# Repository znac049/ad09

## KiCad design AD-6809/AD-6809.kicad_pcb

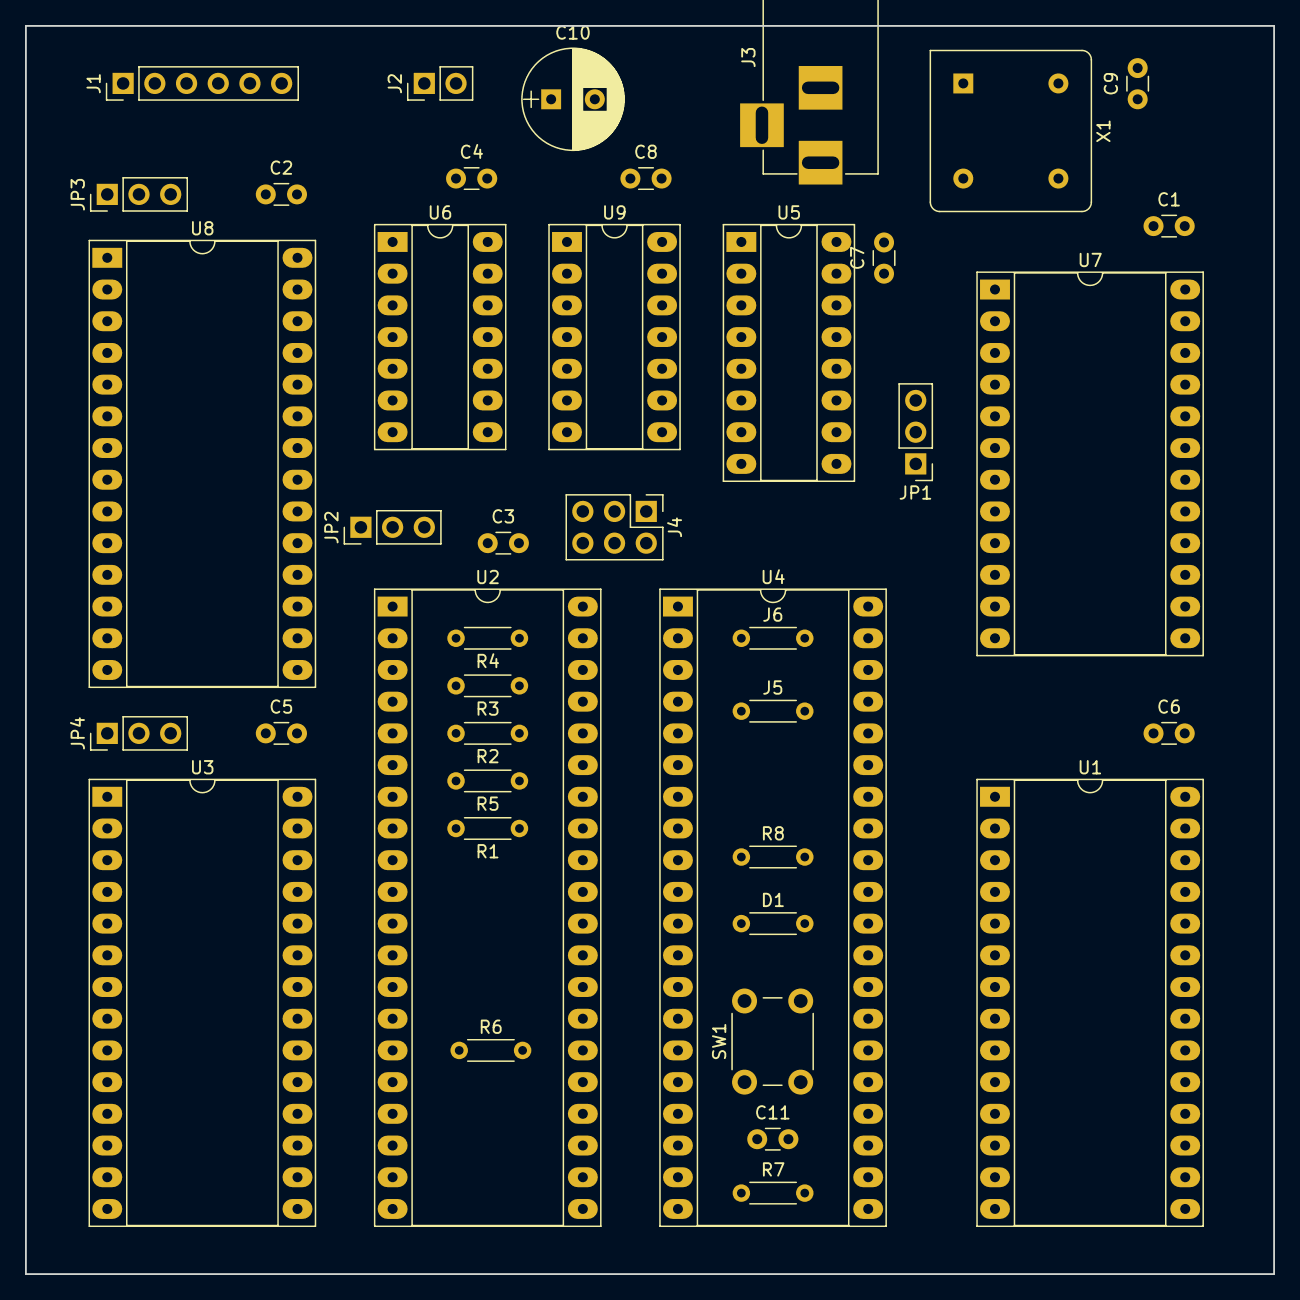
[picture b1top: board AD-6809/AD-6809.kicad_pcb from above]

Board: 2 copper layers, 100.0 x 100.0 mm, 41 parts (0 on the bottom side), 61 nets, no tracks yet.

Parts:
C1, C2, C3, C4, C5, C6, C7, C8, C9: 0.1uF; C_Disc_D3.0mm_W1.6mm_P2.50mm
C10: 470uF; CP_Radial_D8.0mm_P3.50mm
C11: 470nF; C_Disc_D3.0mm_W1.6mm_P2.50mm
D1: IN4148; R_Axial_DIN0204_L3.6mm_D1.6mm_P5.08mm_Horizontal
J1: SERIAL; Socket_Strip_Straight_1x06_Pitch2.54mm
J2: GAMECLK; Socket_Strip_Straight_1x02_Pitch2.54mm
J3: BARREL_JACK
J4: BAUD; Pin_Header_Straight_2x03_Pitch2.54mm
J5: NMI; R_Axial_DIN0204_L3.6mm_D1.6mm_P5.08mm_Horizontal
J6: RESET; R_Axial_DIN0204_L3.6mm_D1.6mm_P5.08mm_Horizontal
JP1: Disable; Socket_Strip_Straight_1x03_Pitch2.54mm
JP2: CLKSRC; Socket_Strip_Straight_1x03_Pitch2.54mm
JP3, JP4: ROM RAM; Socket_Strip_Straight_1x03_Pitch2.54mm
R1, R2, R3, R4, R5, R6, R8: 10K; R_Axial_DIN0204_L3.6mm_D1.6mm_P5.08mm_Horizontal
R7: 100R; R_Axial_DIN0204_L3.6mm_D1.6mm_P5.08mm_Horizontal
SW1: RESET; SW_PUSH_6mm
U1: 28C64; DIP-28_W15.24mm_Socket_LongPads
U2: 6809; DIP-40_W15.24mm_Socket_LongPads
U3, U8: 28C64/IMS1630; DIP-28_W15.24mm_Socket_LongPads
U4: 6502_Header; DIP-40_W15.24mm_Socket_LongPads
U5: 74LS139; DIP-16_W7.62mm_Socket_LongPads
U6: 74LS00; DIP-14_W7.62mm_Socket_LongPads
U7: MC6850; DIP-24_W15.24mm_Socket_LongPads
U9: 74LS93; DIP-14_W7.62mm_Socket_LongPads
X1: 12.288MHz; Oscillator_DIP-8

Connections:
+5V: C1.1, C2.1, C3.1, C4.1, C5.1, C6.1, C7.1, C8.1, C9.1, C10.1, D1.1, J3.1, J5.2, JP3.3, JP4.3, R1.1, R2.1, R3.1, R4.1, R5.1, R8.1, U1.28, U2.7, U3.28, U4.8, U5.16, U6.14, U7.10, U7.12, U8.28, U9.5, X1.1, X1.8
/A0: U1.10, U2.8, U3.10, U4.9, U7.11, U8.10
/A1: U1.9, U2.9, U3.9, U4.10, U8.9
/A2: U1.8, U2.10, U3.8, U4.11, U8.8
/A3: U1.7, U2.11, U3.7, U4.12, U8.7
/A4: U1.6, U2.12, U3.6, U4.13, U8.6
/A5: U1.5, U2.13, U3.5, U4.14, U8.5
/A6: U1.4, U2.14, U3.4, U4.15, U8.4
/A7: U1.3, U2.15, U3.3, U4.16, U8.3
/A8: U1.25, U2.16, U3.25, U4.17, U8.25
/A9: U1.24, U2.17, U3.24, U4.18, U8.24
/A10: U1.21, U2.18, U3.21, U4.19, U8.21
/A11: U1.23, U2.19, U3.23, U4.20, U5.14, U8.23
/A12: U1.2, U2.20, U3.2, U4.22, U5.13, U8.2
/A13: U2.21, U4.23, U5.2
/A14: U2.22, U4.24, U5.3
/A15: JP1.3, U2.23, U4.25, U6.4, U6.5
/CPUCLK: JP2.3, U9.1, U9.12
/D0: U1.11, U2.31, U3.11, U4.33, U7.22, U8.11
/D1: U1.12, U2.30, U3.12, U4.32, U7.21, U8.12
/D2: U1.13, U2.29, U3.13, U4.31, U7.20, U8.13
/D3: U1.15, U2.28, U3.15, U4.30, U7.19, U8.15
/D4: U1.16, U2.27, U3.16, U4.29, U7.18, U8.16
/D5: U1.17, U2.26, U3.17, U4.28, U7.17, U8.17
/D6: U1.18, U2.25, U3.18, U4.27, U7.16, U8.18
/D7: U1.19, U2.24, U3.19, U4.26, U7.15, U8.19
/PHI2: U2.34, U4.39, U6.10, U6.13, U7.14
/R/~W: U2.32, U4.34, U6.1, U6.2, U6.9, U7.13
/RXD: J1.3, U7.2
/SERCLK: J4.2, J4.4, J4.6, U7.3, U7.4
/TXD: J1.2, U7.6
/~A15: U5.1, U6.6
/~FIRQ: R3.2, U2.4
/~IRQ: R4.2, U2.3, U7.7
/~MEM1: U3.20, U5.5
/~MEM2: U5.6, U8.20
/~MEM3: U1.20, U5.7
/~NMI: R6.2, U2.2, U4.6
/~RD: U1.22, U3.22, U6.8, U8.22
/~RESET: J6.2, U2.37, U4.40
/~UART: U5.12, U7.9
/~WR: U1.27, U3.27, U6.11, U8.27
GND: C1.2, C2.2, C3.2, C4.2, C5.2, C6.2, C7.2, C8.2, C9.2, C10.2, C11.2, J1.6, J2.1, J3.2, J3.3, JP1.1, R7.2, U1.14, U2.1, U2.39, U3.14, U4.1, U4.21, U5.8, U6.7, U7.1, U8.14, U9.2, U9.3, U9.10, X1.4
unnamed: C11.1, D1.2, J6.1, R8.2, SW1.2
unnamed: J2.2, JP2.1
unnamed: J4.1, U9.9
unnamed: J4.3, U9.8
unnamed: J4.5, U9.11
unnamed: J5.1, R6.1
unnamed: JP1.2, U7.8
unnamed: JP2.2, U2.38
unnamed: JP3.2, U8.26
unnamed: JP4.2, U3.26
unnamed: R1.2, U2.33
unnamed: R2.2, U2.36
unnamed: R5.2, U2.40
unnamed: R7.1, SW1.1
unnamed: U5.4, U5.15
unnamed: U6.3, U6.12
unnamed: U7.23, U7.24
unnamed: U9.14, X1.5

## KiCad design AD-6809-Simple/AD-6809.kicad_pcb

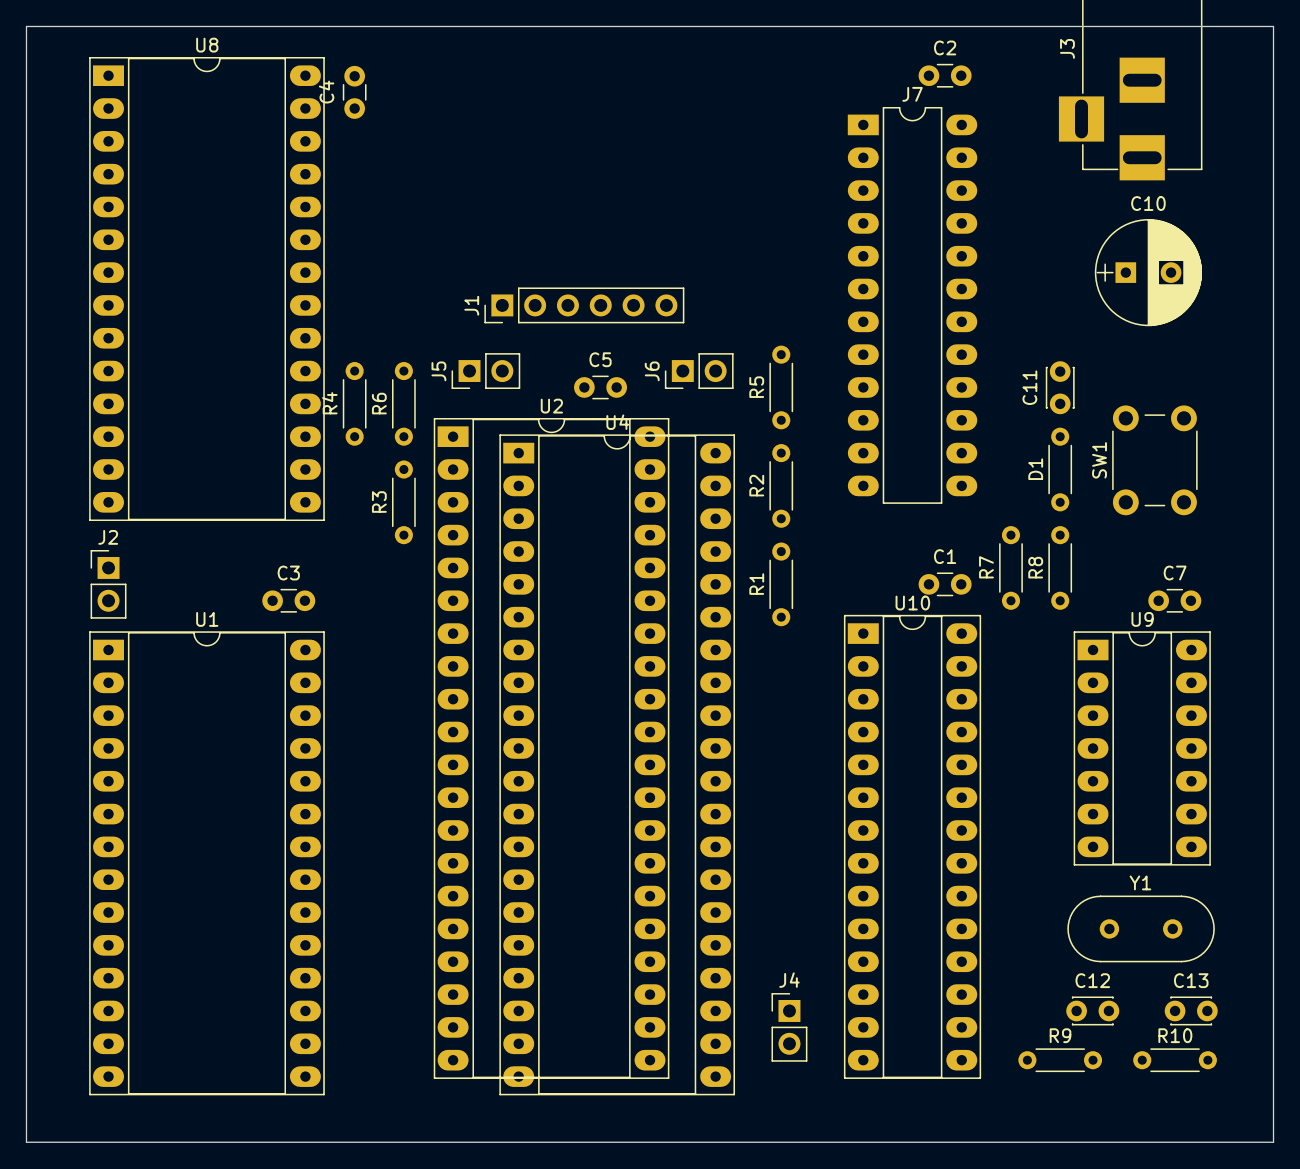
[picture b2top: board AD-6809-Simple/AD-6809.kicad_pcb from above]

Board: 2 copper layers, 96.5 x 86.4 mm, 36 parts (0 on the bottom side), 53 nets, no tracks yet.

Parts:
C1, C2, C3, C4, C5, C7: 0.1uF; C_Disc_D3.0mm_W1.6mm_P2.50mm
C10: 470uF; CP_Radial_D8.0mm_P3.50mm
C11: 470nF; C_Disc_D3.0mm_W2.0mm_P2.50mm
C12, C13: 22pF; C_Disc_D3.0mm_W2.0mm_P2.50mm
D1: IN4148; R_Axial_DIN0204_L3.6mm_D1.6mm_P5.08mm_Horizontal
J1: SERIAL; Socket_Strip_Straight_1x06_Pitch2.54mm
J2: GAMECLK; Socket_Strip_Straight_1x02_Pitch2.54mm
J3: BARREL_JACK
J4: IRQ; Socket_Strip_Straight_1x02_Pitch2.54mm
J5: NMI; Socket_Strip_Straight_1x02_Pitch2.54mm
J6: RESET; Socket_Strip_Straight_1x02_Pitch2.54mm
J7: PAL24; DIP-24_W7.62mm_LongPads
R1, R2, R3, R4, R5, R6, R8: 10K; R_Axial_DIN0204_L3.6mm_D1.6mm_P5.08mm_Horizontal
R7: 100R; R_Axial_DIN0204_L3.6mm_D1.6mm_P5.08mm_Horizontal
R9: 1M0; R_Axial_DIN0204_L3.6mm_D1.6mm_P5.08mm_Horizontal
R10: 1K0; R_Axial_DIN0204_L3.6mm_D1.6mm_P5.08mm_Horizontal
SW1: RESET; SW_PUSH_6mm
U1: 28C64; DIP-28_W15.24mm_Socket_LongPads
U2: 6809; DIP-40_W15.24mm_Socket_LongPads
U4: 6502_Header; DIP-40_W15.24mm_Socket_LongPads
U8: IMS1630; DIP-28_W15.24mm_Socket_LongPads
U9: 74LS04; DIP-14_W7.62mm_Socket_LongPads
U10: SCN2661C; DIP-28_W7.62mm_Socket_LongPads
Y1: 5.0688MHz; Crystal_HC18-U_Vertical

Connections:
+5V: C1.1, C2.1, C3.1, C4.1, C5.1, C7.1, C10.1, D1.1, J3.1, J5.2, J7.24, R1.1, R2.1, R3.1, R4.1, R5.1, R8.1, U1.28, U2.7, U4.8, U8.26, U8.28, U9.14, U10.26
/A0: U1.10, U2.8, U4.9, U8.10, U10.12
/A1: U1.9, U2.9, U4.10, U8.9, U10.10
/A2: U1.8, U2.10, U4.11, U8.8
/A3: U1.7, U2.11, U4.12, U8.7
/A4: U1.6, U2.12, U4.13, U8.6
/A5: U1.5, U2.13, U4.14, U8.5
/A6: U1.4, U2.14, U4.15, U8.4
/A7: U1.3, U2.15, U4.16, U8.3
/A8: U1.25, U2.16, U4.17, U8.25
/A9: U1.24, U2.17, U4.18, U8.24
/A10: U1.21, U2.18, U4.19, U8.21
/A11: J7.2, U1.23, U2.19, U4.20, U8.23
/A12: J7.3, U1.2, U2.20, U4.22, U8.2
/A13: J7.4, U2.21, U4.23
/A14: J7.5, U2.22, U4.24
/A15: J7.6, U2.23, U4.25
/D0: J7.10, U1.11, U2.31, U4.33, U8.11, U10.27
/D1: U1.12, U2.30, U4.32, U8.12, U10.28
/D2: U1.13, U2.29, U4.31, U8.13, U10.1
/D3: U1.15, U2.28, U4.30, U8.15, U10.2
/D4: U1.16, U2.27, U4.29, U8.16, U10.5
/D5: U1.17, U2.26, U4.28, U8.17, U10.6
/D6: U1.18, U2.25, U4.27, U8.18, U10.7
/D7: U1.19, U2.24, U4.26, U8.19, U10.8
/DTR: J1.5, U10.24
/E: J7.7, U2.34, U4.39
/R/~W: J7.8, U2.32, U4.34, U10.13
/RXD: J1.3, U10.3
/SERCLK: U9.6, U10.20
/TXD: J1.2, U10.19
/U_RESET: J7.23, U10.21
/~FIRQ: R3.2, U2.4
/~IRQ: J4.1, R4.2, U2.3
/~NMI: R6.2, U2.2, U4.6
/~RAM_SEL: J7.20, U8.20
/~RD: J7.16, U1.22, U8.22
/~RESET: J6.2, J7.9, U2.37, U4.40
/~ROM_SEL: J7.19, U1.20
/~UART_SEL: J7.21, U10.11
/~WR: J7.17, U1.27, U8.27
GND: C1.2, C2.2, C3.2, C4.2, C5.2, C7.2, C10.2, C11.2, C12.2, C13.2, J1.6, J2.1, J3.2, J3.3, J7.12, R7.2, U1.14, U2.1, U2.39, U4.1, U4.21, U8.14, U9.7, U10.4, U10.16, U10.17
unnamed: C11.1, D1.2, J6.1, R8.2, SW1.2
unnamed: C12.1, R9.2, U9.3, Y1.1
unnamed: C13.1, R10.2, Y1.2
unnamed: J2.2, U2.38
unnamed: J4.2, U10.14, U10.15
unnamed: J5.1, R6.1
unnamed: R1.2, U2.33
unnamed: R2.2, U2.36
unnamed: R5.2, U2.40
unnamed: R7.1, SW1.1
unnamed: R9.1, R10.1, U9.4, U9.5

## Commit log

2017-09-20 6809 specific init added to Reset handler.
2017-09-21 Started commenting the 6502 code.
2017-09-22 Still figuring out the memory test
2017-09-22 Added kicad design, as far as it goes
2017-09-23 Renaming Pokey registers
2017-09-23 Basic init and memory test. Turns on P1 and P2 LEDs if memory error, otherwise LEDs off
2017-09-23 Starting work on the Self Test code once the memory test finishes.
2017-09-23 Enabled 6309 instructions.
    Added two very simple vector generator programs (draw a plus and draw a star). Run one or the other depending on the state of the Selftest switch.
2018-03-26 more test code
2018-03-26 adjusted delay timings
2018-03-26 Created simplified version for initial build
2018-04-09 added padding to the rom
2018-04-09 adding rom binaries to git.
2018-04-19 Padded out the test programs to be rom sized.
2018-04-19 test program
2018-04-20 Added another test file
2018-04-24 Improved the Makefile
